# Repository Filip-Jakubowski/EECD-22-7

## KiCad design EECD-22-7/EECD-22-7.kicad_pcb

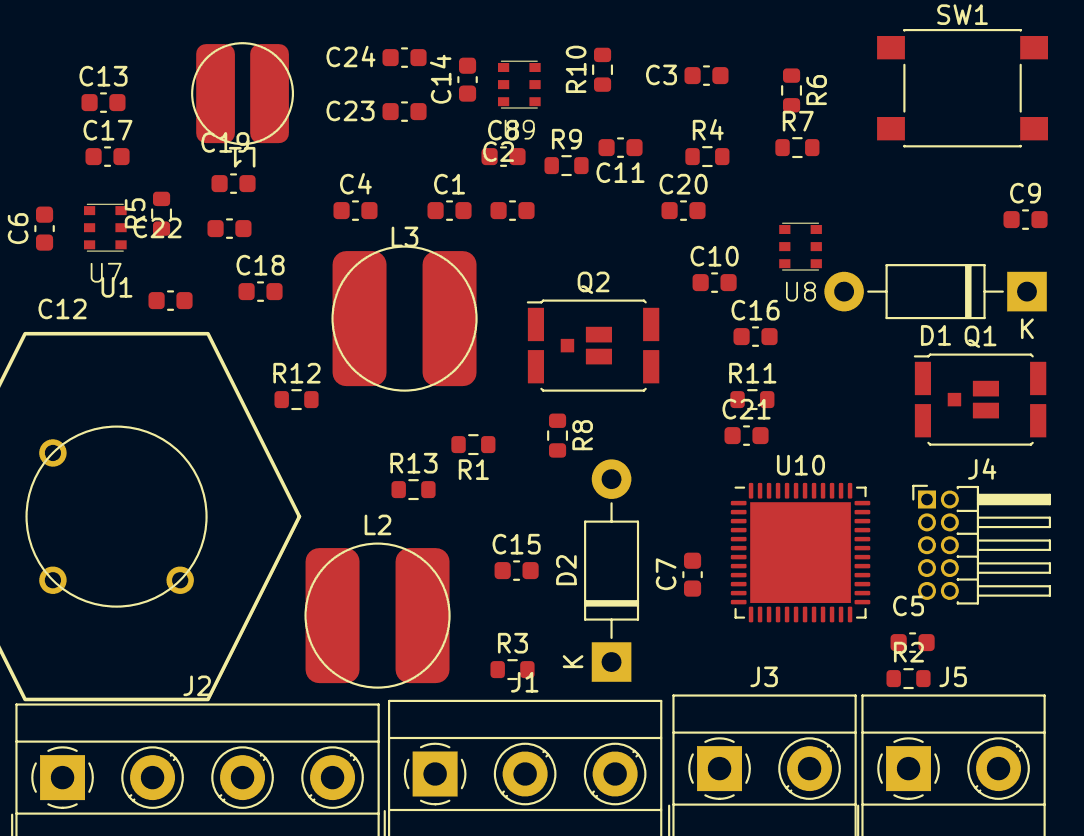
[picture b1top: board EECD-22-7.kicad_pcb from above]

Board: 2 copper layers, 55 parts (0 on the bottom side), 31 nets, no tracks yet.

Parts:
C1, C2, C3, C4, C18, C20, C21, C22, C23: 100nF; C_0603_1608Metric
C5: 0.1uF; C_0603_1608Metric
C6, C10, C14: 100nF 1mR; C_0603_1608Metric
C7: 10uF 4.5 mR; C_0603_1608Metric
C8, C11, C16: 10uF 4.5mR; C_0603_1608Metric
C9, C13: 100nF 3mR; C_0603_1608Metric
C12: 10uF 20mR; C_0603_1608Metric
C15: 10uF 2.2mR; C_0603_1608Metric
C17: 100nF 20mR; C_0603_1608Metric
C19: 10uF; C_0603_1608Metric
C24: 1uF; C_0603_1608Metric
D1, D2: 1N4004; D_DO-41_SOD81_P10.16mm_Horizontal
J1: Screw_Terminal_01x03; TerminalBlock_MetzConnect_Type055_RT01503HDWU_1x03_P5.00mm_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
J2: Screw_Terminal_01x04; TerminalBlock_MetzConnect_Type055_RT01504HDWU_1x04_P5.00mm_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
J3, J5: Screw_Terminal_01x02; TerminalBlock_MetzConnect_Type055_RT01502HDWU_1x02_P5.00mm_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
J4: Conn_ARM_JTAG_SWD_10; PinHeader_2x05_P1.27mm_Horizontal
L1: 12uH 100mR 1.6A; NPI54C120MTRF
L2: 15uH 90mR 1.6A; NPI75C150MTRF
L3: 15uH 90mR 1.8A; NPI75C150MTRF
Q1, Q2: IRF6616; DirectFET_MX
R1: 4.7KR; R_0603_1608Metric
R2: 100R; R_0603_1608Metric
R3: 470k; R_0603_1608Metric
R4: 70kR; R_0603_1608Metric
R5, R7, R10: 22kR; R_0603_1608Metric
R6: 309kR; R_0603_1608Metric
R8, R11, R12: 10kR; R_0603_1608Metric
R9: 115kR; R_0603_1608Metric
R13: 500kR; R_0603_1608Metric
SW1: SW_Push; SW_Push_1P1T_NO_6x6mm_H9.5mm
U1: 4002B; m12con
U7, U8, U9: LMR54406DBVR; lmr
U10: STM32F103CBUx; QFN-48-1EP_7x7mm_P0.5mm_EP5.6x5.6mm

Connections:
3.3V_GND: C19.2, C20.2, C21.2, C22.2, U10.23 (VSS), U10.35 (VSS), U10.47 (VSS), U10.49 (VSS)
+3.3V: C7.1, C19.1, C20.1, C21.1, C22.1, C23.1, C24.1, J4.1 (VTref), L1.2, R4.1, SW1.1, U10.1 (VBAT), U10.9 (VDDA), U10.24 (VDD), U10.36 (VDD), U10.48 (VDD)
+5V: C1.1, C4.1, C15.1, J1.1, J2.1, L3.2, R1.1, R9.1
+12V: C2.1, C3.1, C11.1, L2.2, R6.1
+BATT: C8.1, C9.1, C12.1, C13.1, C16.1, C17.1, J3.1, U7.2 (VIN), U7.3 (EN), U8.2 (VIN), U8.3 (EN), U9.2 (VIN), U9.3 (EN)
GND12V: C1.2, C2.2, C3.2, C4.2, C7.2, C8.2, C9.2, C11.2, C12.2, C13.2, C15.2, C16.2, C17.2, C18.1, C23.2, C24.2, D1.1 (K), D2.2 (A), J1.2, J2.2, J3.2, J4.3 (GND), J4.5 (GND), J5.2, Q1.1 (D), Q1.3 (S), Q2.1 (D), Q2.3 (S), R3.2, R5.2, R7.2, R8.1, R10.2, R11.1, R13.2, U7.6 (GND), U8.6 (GND), U9.6 (GND), U10.8 (VSSA)
I2C_1_CLK: J2.4, U10.42 (PB6)
I2C_1_SDA: J2.3, U10.43 (PB7)
unnamed: J5.1, R2.2, R3.1
unnamed: C5.2, D1.2 (A), D2.1 (K), R2.1
unnamed: C6.1, L1.1, U7.4 (SW)
unnamed: C6.2, U7.1 (CB)
unnamed: C10.1, L2.1, U8.4 (SW)
unnamed: C10.2, U8.1 (CB)
unnamed: C14.1, L3.1, U9.4 (SW)
unnamed: C14.2, U9.1 (CB)
unnamed: C18.2, R12.1, U10.44 (BOOT0)
unnamed: R4.2, R5.1, U7.5 (FB)
unnamed: R6.2, R7.1, U8.5 (FB)
unnamed: R9.2, R10.1, U9.5 (FB)
unnamed: R12.2, R13.1, SW1.2
RST: J4.10 (~RESET), U10.7 (NRST)
SWDIO: J4.2 (SWDIO/TMS), U10.34 (PA13)
SWDLK: J4.4 (SWDCLK/TCK), U10.37 (PA14)
TDI: J4.8 (NC/TDI), U10.38 (PA15)
TDO: J4.6 (SWO/TDO), U10.39 (PB3)
acoustic: C5.1, U10.20 (PB2)
peri_power_1: Q1.2 (G), R8.2, U10.41 (PB5)
peri_power_2: Q2.2 (G), R11.2, U10.45 (PB8)
pres: U1.2 (OUT_PCB,), U10.19 (PB1)
temper: J1.3, R1.2, U10.18 (PB0)

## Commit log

2022-12-06 Create interfaces
2022-12-06 Rename interfaces to interfaces.txt
